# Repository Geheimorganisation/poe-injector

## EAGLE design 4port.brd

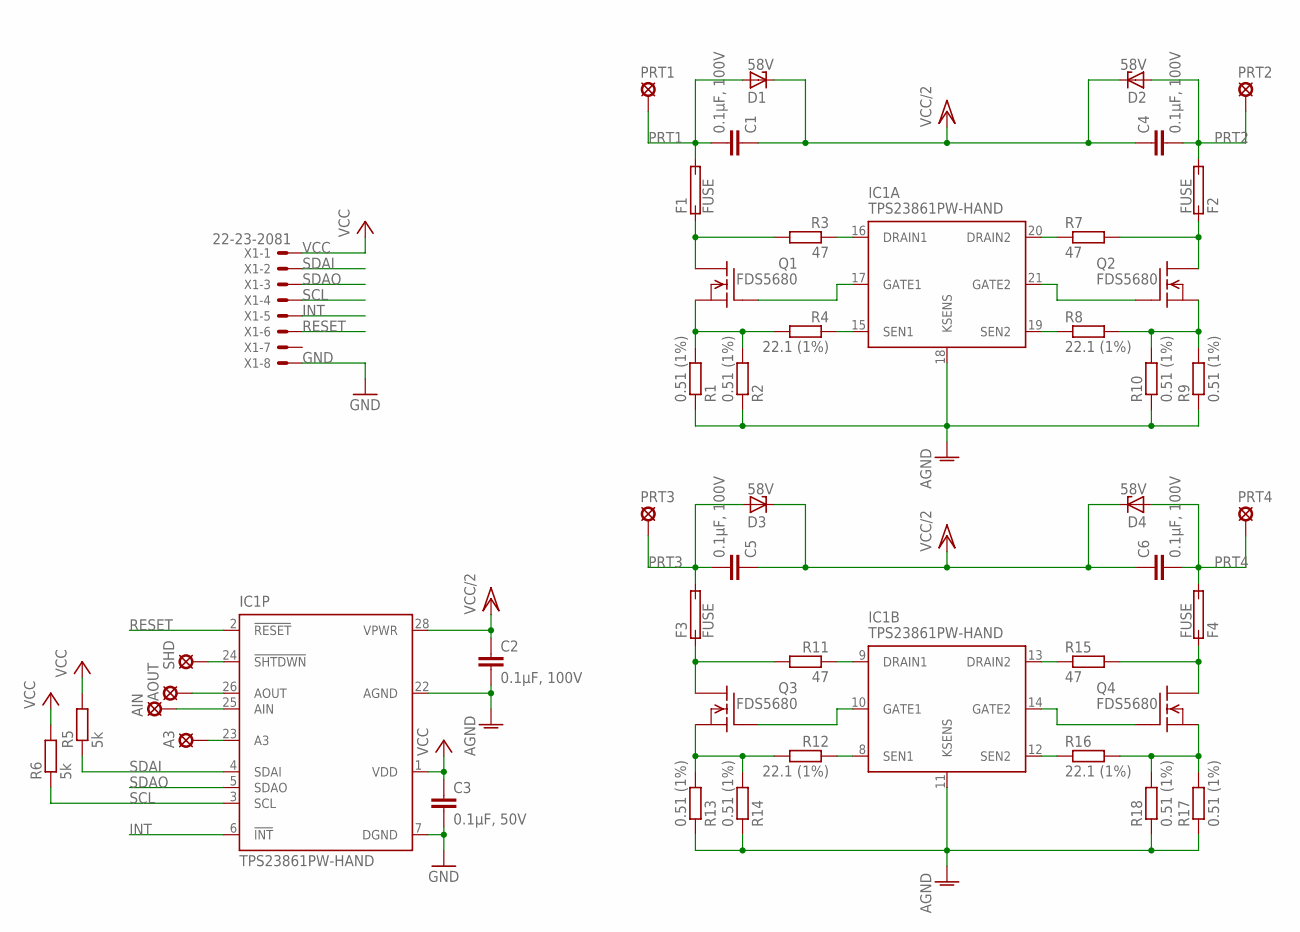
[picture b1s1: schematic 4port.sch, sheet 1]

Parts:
A3: SE14
AIN: SE14
AOUT: SE14
C1, C2, C4, C5, C6: 0.1µF, 100V; C0805K
C3: 0.1µF, 50V; C0805K
D1, D2, D3, D4: 58V; SMB
F1, F2, F3, F4: FUSE; R1206W
IC1: TPS23861PW-HAND; PW_R-PDSO-G28_HAND
PRT1, PRT2, PRT3, PRT4: SE14
Q1, Q2, Q3, Q4: FDS5680; SO-8
R1, R2, R9, R10, R13, R14, R17, R18: 0.51 (1%); R0603
R3, R7, R11, R15: 47; R0603
R4, R8, R12, R16: 22.1 (1%); R0603
R5, R6: 5k; R0805W
SHD: SE14
X1: 22-23-2081

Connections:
AGND: C2.2, IC1.11 (KSENS), IC1.18 (KSENS), IC1.22 (AGND), R1.1, R2.1, R9.1, R10.1, R13.1, R14.1, R17.1, R18.1
GND: C3.2, IC1.7 (DGND), X1.8; also elsewhere on the board
INT: IC1.6 (!INT), X1.5
unnamed: IC1.16 (DRAIN1), R3.1
unnamed: IC1.15 (SEN1), R4.1
unnamed: Q1.1 (S), Q1.2 (S), Q1.3 (S), R1.2, R2.2, R4.2
unnamed: IC1.17 (GATE1), Q1.4 (G)
unnamed: IC1.20 (DRAIN2), R7.1
unnamed: AOUT.MP, IC1.26 (AOUT)
unnamed: AIN.MP, IC1.25 (AIN)
unnamed: A3.MP, IC1.23 (A3)
unnamed: IC1.24 (!SHTDWN), SHD.MP
unnamed: IC1.19 (SEN2), R8.1
unnamed: Q2.1 (S), Q2.2 (S), Q2.3 (S), R8.2, R9.2, R10.2
unnamed: IC1.21 (GATE2), Q2.4 (G)
unnamed: IC1.9 (DRAIN1), R11.1
unnamed: IC1.8 (SEN1), R12.1
unnamed: Q3.1 (S), Q3.2 (S), Q3.3 (S), R12.2, R13.2, R14.2
unnamed: IC1.10 (GATE1), Q3.4 (G)
unnamed: IC1.13 (DRAIN2), R15.1
unnamed: IC1.12 (SEN2), R16.1
unnamed: Q4.1 (S), Q4.2 (S), Q4.3 (S), R16.2, R17.2, R18.2
unnamed: IC1.14 (GATE2), Q4.4 (G)
unnamed: F1.1 (1A), Q1.5 (D), Q1.6 (D), Q1.7 (D), Q1.8 (D), R3.2
unnamed: F2.1 (1A), Q2.5 (D), Q2.6 (D), Q2.7 (D), Q2.8 (D), R7.2
unnamed: F3.1 (1A), Q3.5 (D), Q3.6 (D), Q3.7 (D), Q3.8 (D), R11.2
unnamed: F4.1 (1A), Q4.5 (D), Q4.6 (D), Q4.7 (D), Q4.8 (D), R15.2
PRT1: C1.2, D1.A, F1.2 (2A), PRT1.MP; also elsewhere on the board
PRT2: C4.2, D2.A, F2.2 (2A), PRT2.MP; also elsewhere on the board
PRT3: C5.2, D3.A, F3.2 (2A), PRT3.MP; also elsewhere on the board
PRT4: C6.2, D4.A, F4.2 (2A), PRT4.MP; also elsewhere on the board
RESET: IC1.2 (!RESET), X1.6
SCL: IC1.3 (SCL), R6.1, X1.4
SDAI: IC1.4 (SDAI), R5.1, X1.2
SDAO: IC1.5 (SDAO), X1.3
VCC: C3.1, IC1.1 (VDD), R5.2, R6.2, X1.1
VCC/2: C1.1, C2.1, C4.1, C5.1, C6.1, D1.C, D2.C, D3.C, D4.C, IC1.28 (VPWR); also elsewhere on the board

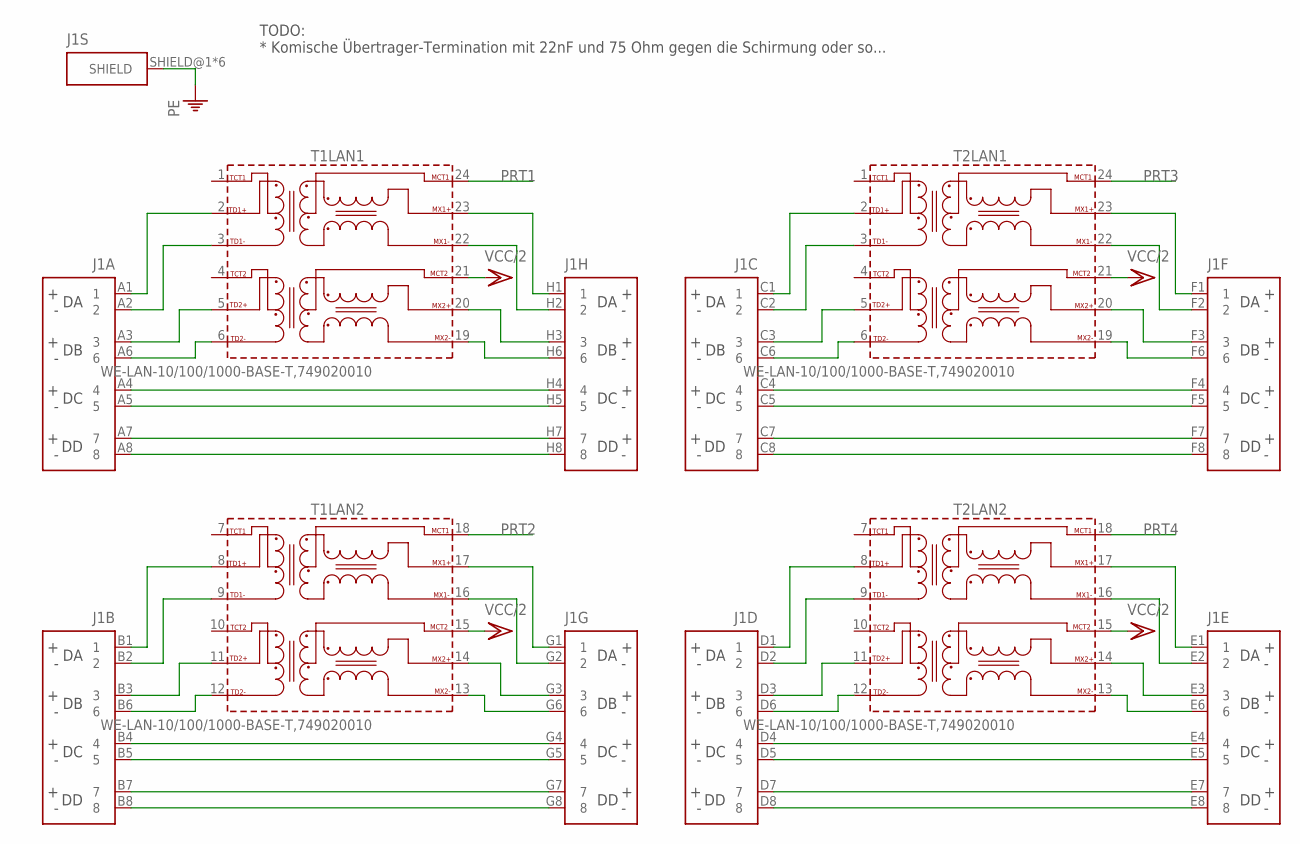
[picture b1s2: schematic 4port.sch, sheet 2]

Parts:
J1: 615064243321
T1, T2: WE-LAN-10/100/1000-BASE-T,749020010; 749020010

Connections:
unnamed: J1.A4 (4), J1.H4 (4)
unnamed: J1.A5 (5), J1.H5 (5)
unnamed: J1.A7 (7), J1.H7 (7)
unnamed: J1.A8 (8), J1.H8 (8)
unnamed: J1.A6 (6), T1.6 (TD2-)
unnamed: J1.A3 (3), T1.5 (TD2+)
unnamed: J1.A2 (2), T1.3 (TD1-)
unnamed: J1.A1 (1), T1.2 (TD1+)
unnamed: J1.H6 (6), T1.19 (MX2-)
unnamed: J1.H3 (3), T1.20 (MX2+)
unnamed: J1.H2 (2), T1.22 (MX1-)
unnamed: J1.H1 (1), T1.23 (MX1+)
unnamed: J1.B4 (4), J1.G4 (4)
unnamed: J1.B5 (5), J1.G5 (5)
unnamed: J1.B7 (7), J1.G7 (7)
unnamed: J1.B8 (8), J1.G8 (8)
unnamed: J1.B6 (6), T1.12 (TD2-)
unnamed: J1.B3 (3), T1.11 (TD2+)
unnamed: J1.B2 (2), T1.9 (TD1-)
unnamed: J1.B1 (1), T1.8 (TD1+)
unnamed: J1.G6 (6), T1.13 (MX2-)
unnamed: J1.G3 (3), T1.14 (MX2+)
unnamed: J1.G2 (2), T1.16 (MX1-)
unnamed: J1.G1 (1), T1.17 (MX1+)
unnamed: J1.C4 (4), J1.F4 (4)
unnamed: J1.C5 (5), J1.F5 (5)
unnamed: J1.C7 (7), J1.F7 (7)
unnamed: J1.C8 (8), J1.F8 (8)
unnamed: J1.C6 (6), T2.6 (TD2-)
unnamed: J1.C3 (3), T2.5 (TD2+)
unnamed: J1.C2 (2), T2.3 (TD1-)
unnamed: J1.C1 (1), T2.2 (TD1+)
unnamed: J1.F6 (6), T2.19 (MX2-)
unnamed: J1.F3 (3), T2.20 (MX2+)
unnamed: J1.F2 (2), T2.22 (MX1-)
unnamed: J1.F1 (1), T2.23 (MX1+)
unnamed: J1.D4 (4), J1.E4 (4)
unnamed: J1.D5 (5), J1.E5 (5)
unnamed: J1.D7 (7), J1.E7 (7)
unnamed: J1.D8 (8), J1.E8 (8)
unnamed: J1.D6 (6), T2.12 (TD2-)
unnamed: J1.D3 (3), T2.11 (TD2+)
unnamed: J1.D2 (2), T2.9 (TD1-)
unnamed: J1.D1 (1), T2.8 (TD1+)
unnamed: J1.E6 (6), T2.13 (MX2-)
unnamed: J1.E3 (3), T2.14 (MX2+)
unnamed: J1.E2 (2), T2.16 (MX1-)
unnamed: J1.E1 (1), T2.17 (MX1+)
PE: J1.SHIELD@1 (SHIELD), J1.SHIELD@2 (SHIELD), J1.SHIELD@3 (SHIELD), J1.SHIELD@4 (SHIELD), J1.SHIELD@5 (SHIELD), J1.SHIELD@6 (SHIELD)
PRT1: T1.24 (MCT1); also elsewhere on the board
PRT2: T1.18 (MCT1); also elsewhere on the board
PRT3: T2.24 (MCT1); also elsewhere on the board
PRT4: T2.18 (MCT1); also elsewhere on the board
VCC/2: T1.15 (MCT2), T1.21 (MCT2), T2.15 (MCT2), T2.21 (MCT2); also elsewhere on the board

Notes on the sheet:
TODO: * Komische Übertrager-Termination mit 22nF und 75 Ohm gegen die Schirmung oder so...

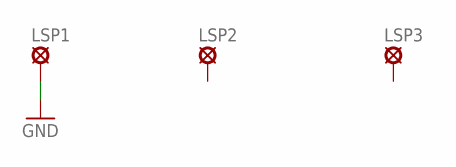
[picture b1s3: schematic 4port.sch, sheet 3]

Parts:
LSP1, LSP2, LSP3: SE14

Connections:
GND: LSP1.MP; also elsewhere on the board

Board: 2 copper layers, 52 parts (0 on the bottom side), 86 nets, no tracks yet.

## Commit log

2016-06-26 initial
